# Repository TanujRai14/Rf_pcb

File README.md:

📡 STM32 + nRF24L01P USB Dongle (4-Layer PCB)

This project implements a USB-based transceiver dongle using the STM32L432 MCU and nRF24L01P RF module.
The board is designed as a 4-layer PCB optimized for USB high-speed signaling and RF performance.

🔧 Features

MCU: STM32L432KBU6 (Cortex-M4, USB support, low-power).

RF Transceiver: nRF24L01P with SMA antenna connector.

USB Interface: Micro USB-B with ESD protection.

Power Regulation: Onboard 3.3V regulator with USB +5V input.

Programming & Debugging: SWD connector for firmware upload/debug.

Clocking: 16 MHz crystal oscillator for the transceiver.

⚡️ PCB Design Notes

This design follows best practices for mixed-signal (USB + RF) high-speed boards:

4-Layer Stackup

Layer 1: Signal

Layer 2: Ground plane

Layer 3: Power plane + signal

Layer 4: Signal

➝ Provides controlled impedance routing and solid ground return paths.

USB Differential Pair

Routed as 90 Ω differential impedance.

Length matched using squiggle traces for proper signal timing.

Minimal via usage to reduce reflections.

Crystal Oscillator

No ground plane directly beneath the crystal to avoid damping oscillations.

RF Section

50 Ω controlled impedance routing to the SMA connector.

Antenna matching network (L-C components) placed close to RF pin.

Short traces and minimized via count for RF integrity.

Decoupling & Power Integrity

Multiple ceramic capacitors (100nF, 1µF, 10µF) placed near VDD pins.

Bulk capacitor on regulator output for stability.

Power traces kept short and wide to reduce IR drop.

Grounding

Continuous solid GND plane on Layer 2.

Stitching vias placed around high-speed and RF sections.

Segregation of analog/RF and digital sections to reduce noise coupling.

Other Notes

ESD protection diodes added on USB lines.

Reset capacitor for parasitic reset protection.

Careful placement of SWD pins for easy programming access.

🚀 Getting Started

Connect the board via USB Micro-B cable.

Flash firmware via SWD programmer (ST-Link, J-Link, etc.).

Use the USB interface for communication and debugging.

Attach an SMA antenna to nRF24L01P for wireless operation.

📌 To-Do / Future Improvements

 Add test points for power rails.

 Consider shielding can for RF section.

 Explore USB Type-C instead of Micro-B.

 Improve thermal relief on regulator section.

👤 Designer: Tanuj Rai
🛠 Tools Used: KiCad (schematic & PCB), 4-layer controlled impedance design.# Rf_pcb

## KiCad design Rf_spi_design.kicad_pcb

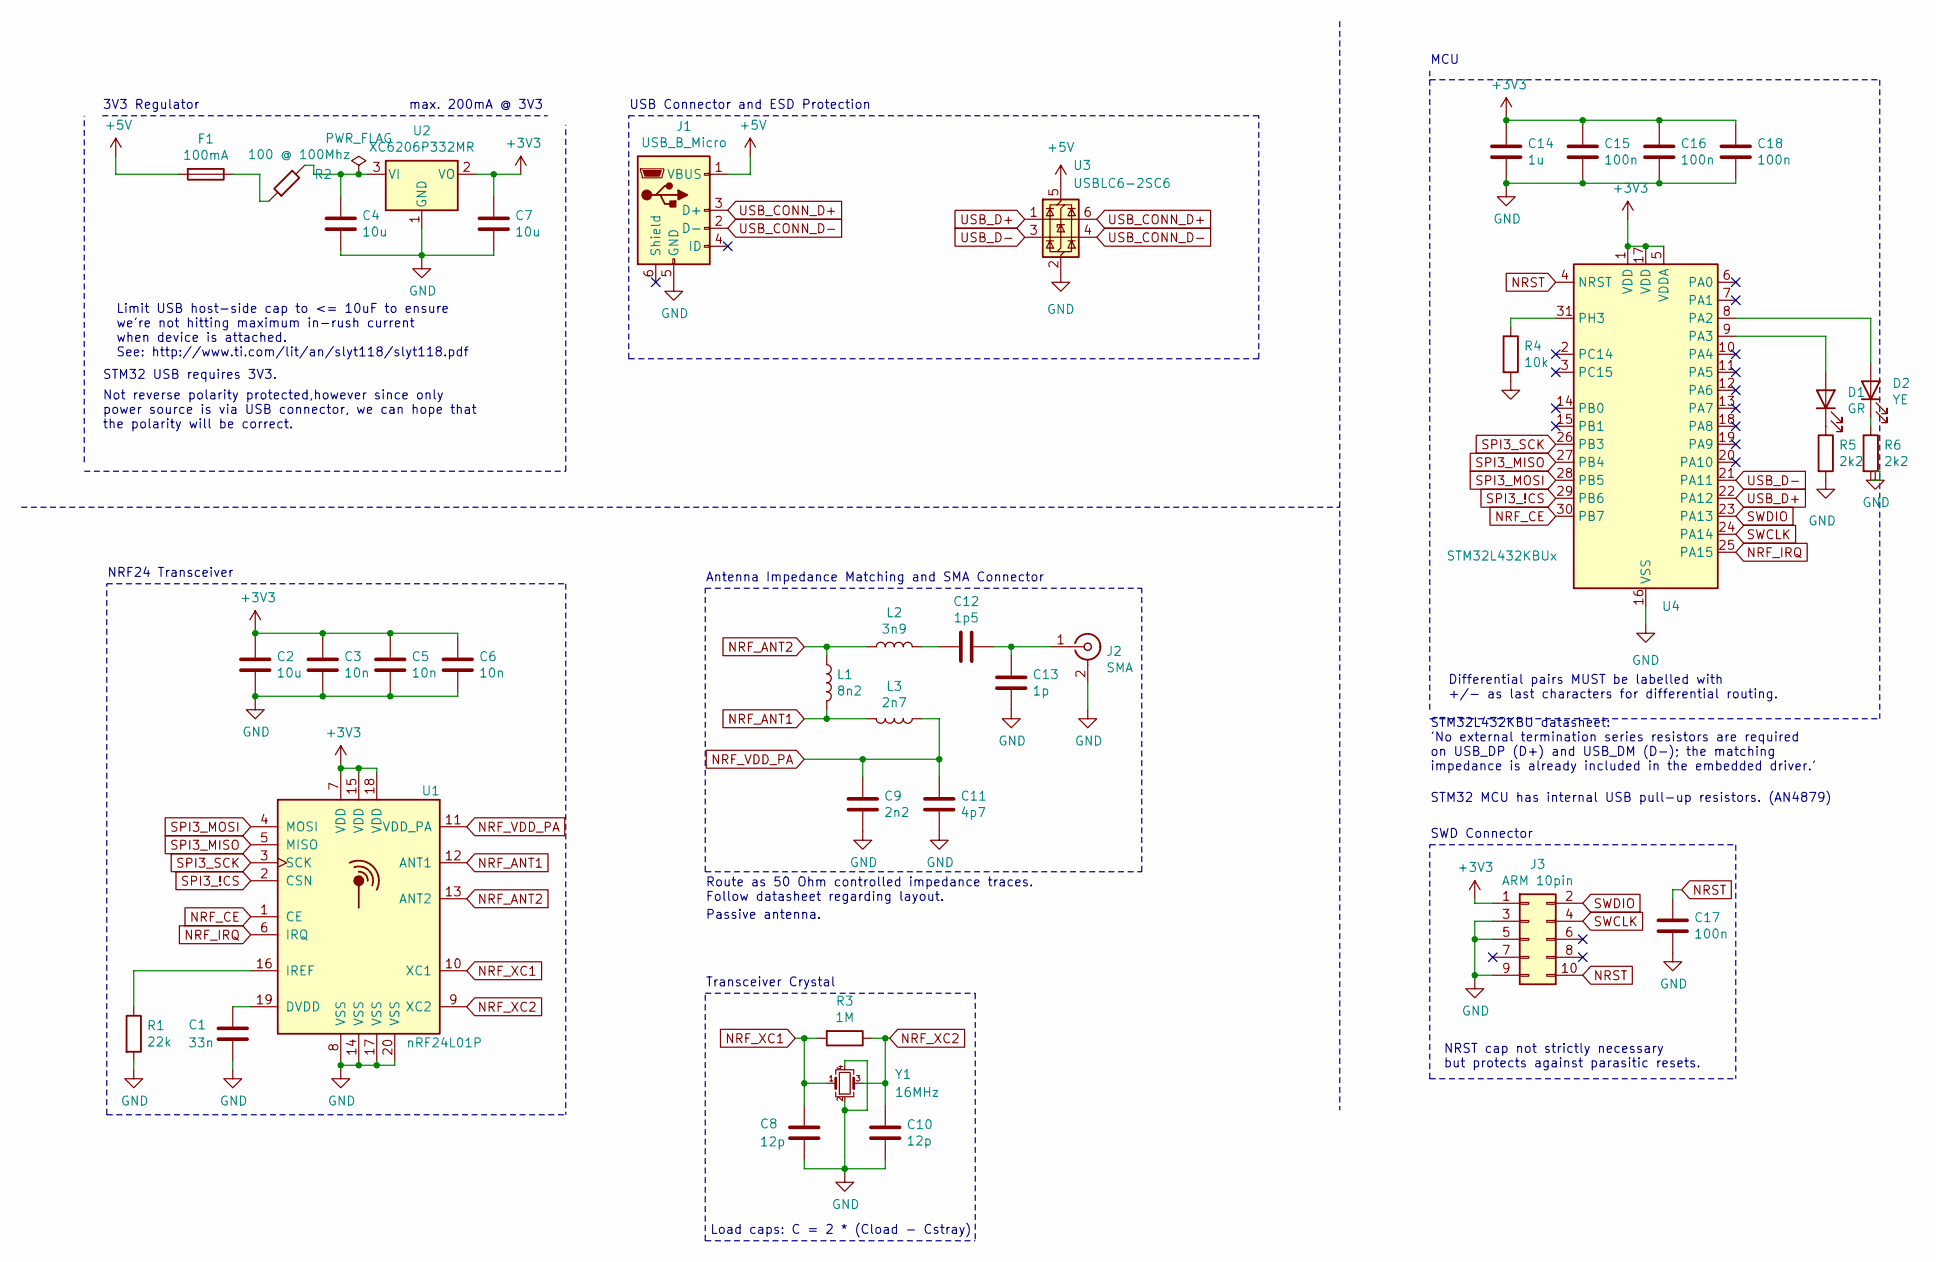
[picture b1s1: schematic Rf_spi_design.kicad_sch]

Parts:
C1: 33n; C_0402_1005Metric
C2, C4, C7: 10u; C_0603_1608Metric
C3, C5, C6: 10n; C_0402_1005Metric
C8, C10: 12p; C_0402_1005Metric
C9: 2n2; C_0402_1005Metric
C11: 4p7; C_0402_1005Metric
C12: 1p5; C_0402_1005Metric
C13: 1p; C_0402_1005Metric
C14: 1u; C_0402_1005Metric
C15, C16, C17, C18: 100n; C_0402_1005Metric
D1: GR; LED_0603_1608Metric
D2: YE; LED_0603_1608Metric
F1: 100mA; Fuse_1206_3216Metric
J1: USB_B_Micro; USB_Micro-B_Amphenol_10118193-0001LF_Horizontal
J2: SMA; BNC_Amphenol_031-6575_Horizontal
J3: ARM 10pin; PinHeader_2x05_P1.27mm_Vertical
L1: 8n2; L_0402_1005Metric
L2: 3n9; L_0402_1005Metric
L3: 2n7; L_0402_1005Metric
R1: 22k; R_0402_1005Metric
R2: 100 @ 100Mhz; R_0805_2012Metric
R3: 1M; R_0402_1005Metric
R4: 10k; R_0402_1005Metric
R5, R6: 2k2; R_0603_1608Metric
U1: nRF24L01P; QFN-20-1EP_4x4mm_P0.5mm_EP2.5x2.5mm
U2: XC6206P332MR; SOT-23
U3: USBLC6-2SC6; SOT-23-6
U4: STM32L432KBUx; QFN-32-1EP_5x5mm_P0.5mm_EP3.45x3.45mm
Y1: 16MHz; Crystal_SMD_3225-4Pin_3.2x2.5mm

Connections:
+3V3: C2.1, C3.1, C5.1, C6.1, C7.1, C14.1, C15.1, C16.1, C18.1, J3.1, U1.7 (VDD), U1.15 (VDD), U1.18 (VDD), U2.2 (VO), U4.1 (VDD), U4.5 (VDDA), U4.17 (VDD)
+5V: F1.2, J1.1 (VBUS), U3.5 (VBUS)
GND: C1.2, C2.2, C3.2, C4.2, C5.2, C6.2, C7.2, C8.2, C9.1, C10.2, C11.1, C13.1, C14.2, C15.2, C16.2, C17.2, C18.2, J1.5 (GND), J2.2 (Ext), J3.3, J3.5, J3.9, R1.2, R4.2, R5.2, R6.2, U1.8 (VSS), U1.14 (VSS), U1.17 (VSS), U1.20 (VSS), U2.1 (GND), U3.2 (GND), U4.16 (VSS), U4.32 (VSS), U4.33 (VSS), Y1.2, Y1.4
NRF_ANT1: L1.2, L3.2, U1.12 (ANT1)
NRF_ANT2: L1.1, L2.1, U1.13 (ANT2)
NRF_CE: U1.1 (CE), U4.30 (PB7)
NRF_IRQ: U1.6 (IRQ), U4.25 (PA15)
NRF_VDD_PA: C9.2, C11.2, L3.1, U1.11 (VDD_PA)
NRF_XC1: C8.1, R3.2, U1.10 (XC1), Y1.1
NRF_XC2: C10.1, R3.1, U1.9 (XC2), Y1.3
NRST: C17.1, J3.10, U4.4 (NRST)
unnamed: C12.2, L2.2
unnamed: D1.2 (A), U4.9 (PA3)
unnamed: D1.1 (K), R5.1
unnamed: D2.2 (A), U4.8 (PA2)
unnamed: D2.1 (K), R6.1
unnamed: F1.1, R2.1
unnamed: C12.1, C13.2, J2.1 (In)
unnamed: C1.1, U1.19 (DVDD)
unnamed: R1.1, U1.16 (IREF)
unnamed: C4.1, R2.2, U2.3 (VI)
unnamed: R4.1, U4.31 (PH3)
SPI3_!CS: U1.2 (CSN), U4.29 (PB6)
SPI3_MISO: U1.5 (MISO), U4.27 (PB4)
SPI3_MOSI: U1.4 (MOSI), U4.28 (PB5)
SPI3_SCK: U1.3 (SCK), U4.26 (PB3)
SWCLK: J3.4, U4.24 (PA14)
SWDIO: J3.2, U4.23 (PA13)
USB_CONN_D+: J1.3 (D+), U3.6 (I/O1)
USB_CONN_D-: J1.2 (D-), U3.4 (I/O2)
USB_D+: U3.1 (I/O1), U4.22 (PA12)
USB_D-: U3.3 (I/O2), U4.21 (PA11)

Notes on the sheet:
Differential pairs MUST be labelled with +/- as last characters for differential routing.
Not reverse polarity protected,however since only power source is via USB connector, we can hope that the polarity will be correct.
Passive antenna.
NRF24 Transceiver
Transceiver Crystal
STM32L432KBU datasheet: 'No external termination series resistors are required on USB_DP (D+) and USB_DM (D-); the matching impedance is already included in the embedded driver.'
3V3 Regulator
Antenna Impedance Matching and SMA Connector
Route as 50 Ohm controlled impedance traces. Follow datasheet regarding layout.
Load caps: C = 2 * (Cload - Cstray)
Limit USB host-side cap to <= 10uF to ensure we're not hitting maximum in-rush current when device is attached. See: http://www.ti.com/lit/an/slyt118/slyt118.pdf
SWD Connector
MCU
STM32 MCU has internal USB pull-up resistors. (AN4879)
NRST cap not strictly necessary but protects against parasitic resets.
max. 200mA @ 3V3
USB Connector and ESD Protection
STM32 USB requires 3V3.

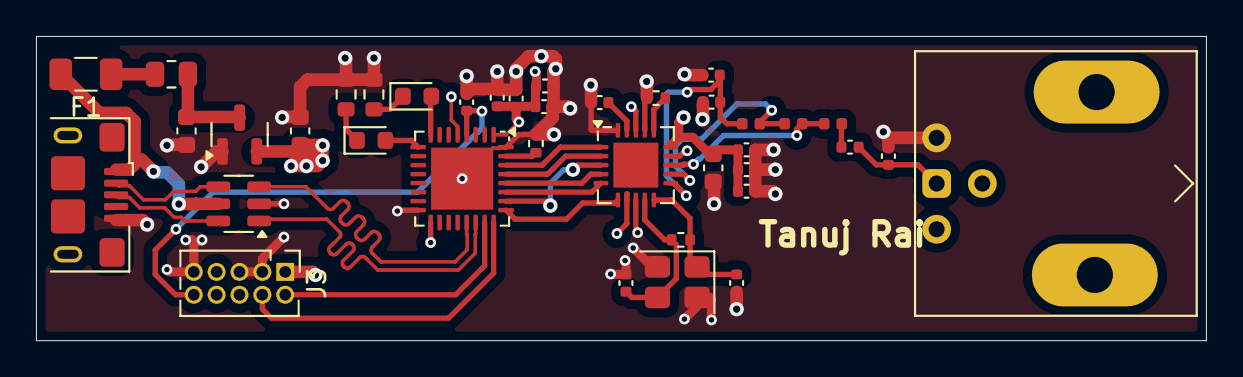
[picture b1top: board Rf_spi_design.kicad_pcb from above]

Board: 4 copper layers, 65.0 x 16.9 mm, 38 parts (0 on the bottom side), 32 nets.
